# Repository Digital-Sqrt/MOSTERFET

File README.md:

***
# MOSTERFET is covered by the Creative Commons Attribution-ShareAlike 3.0 Unported License.
 Low cost duel MOSFET driver for heated beds and hot ends.  Both Channels are electrically isolated from each other.

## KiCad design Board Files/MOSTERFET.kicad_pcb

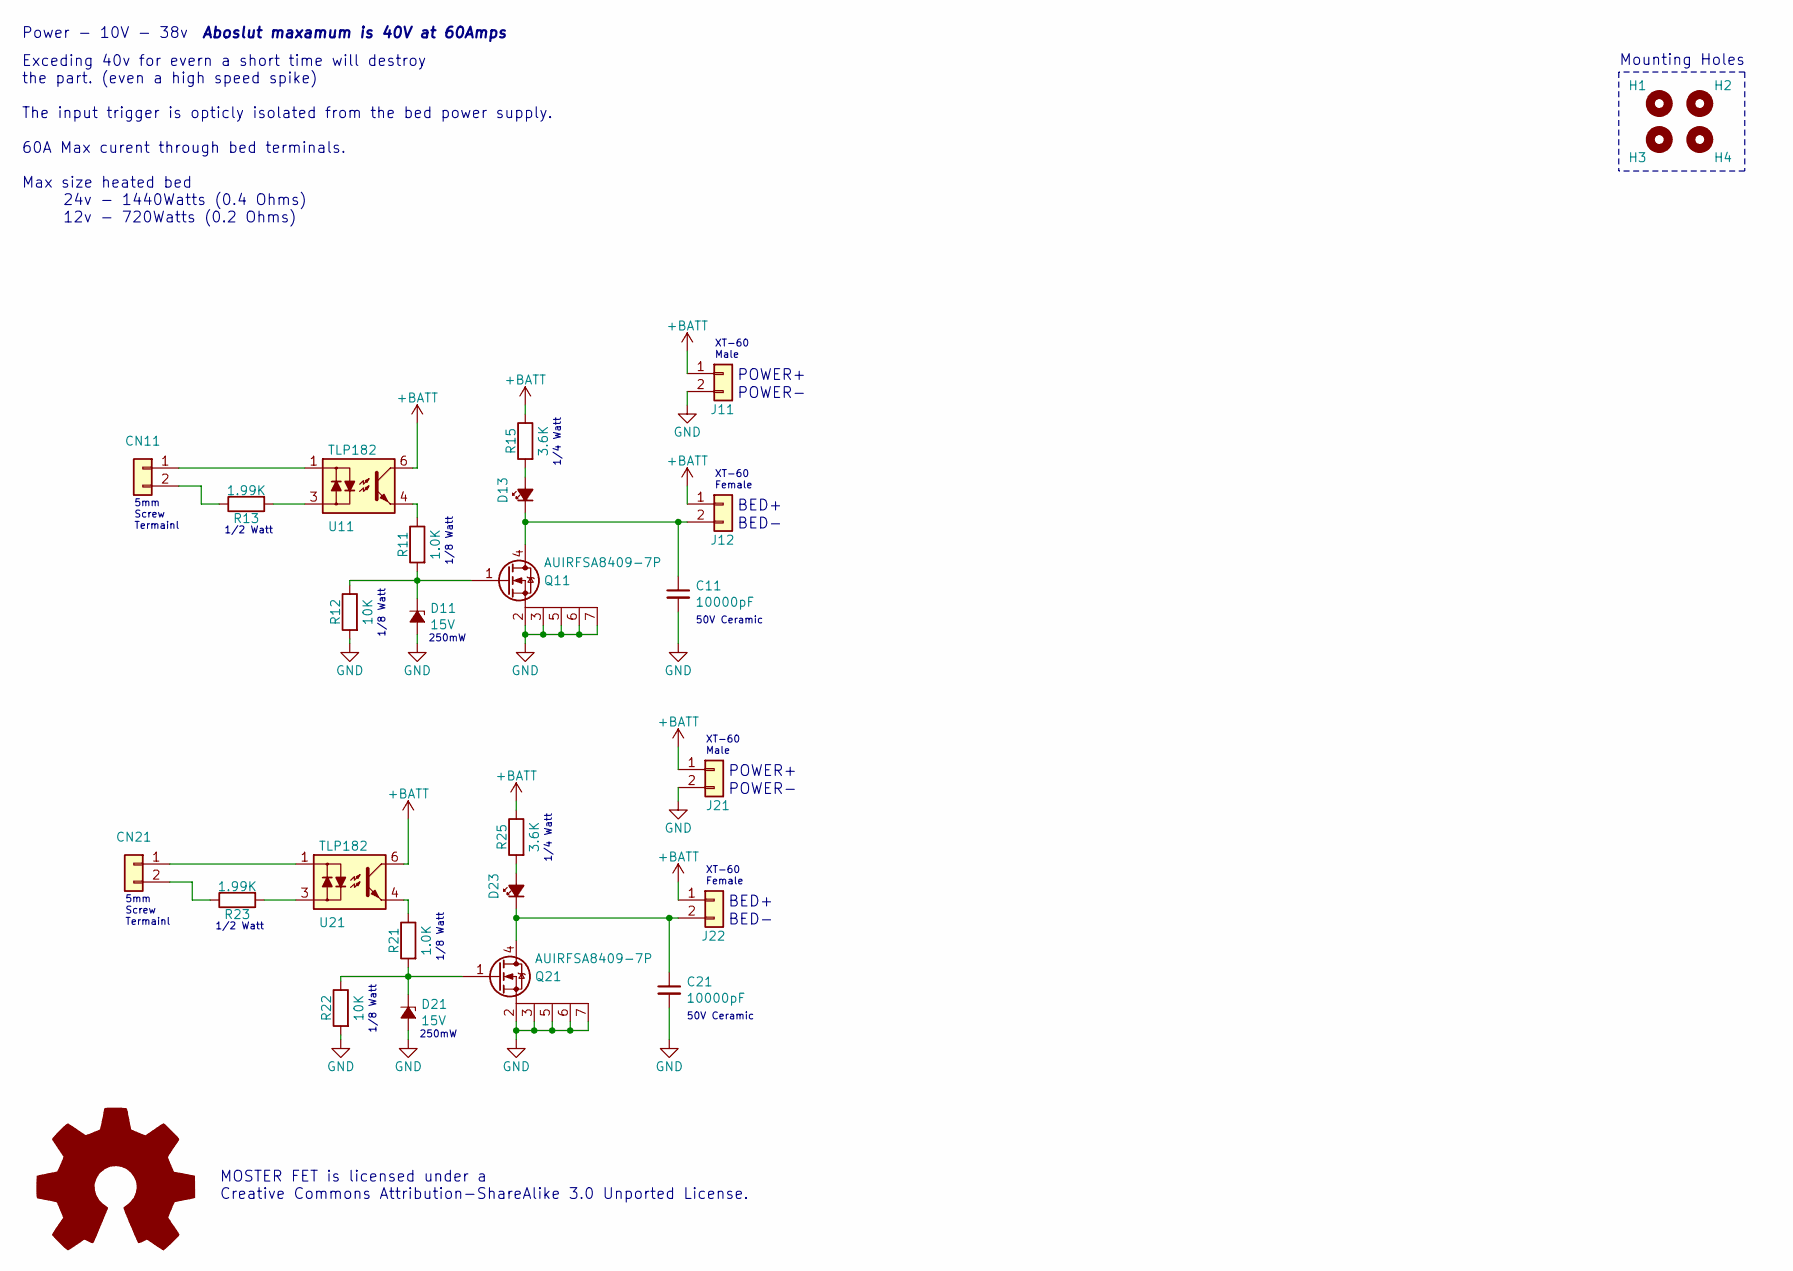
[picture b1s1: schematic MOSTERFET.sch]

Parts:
C11, C21: 10000pF; C_0805_HandSoldering
CN11, CN21: Jumper_NC_Small; JST_NV_B02P-NV_2x5.00mm_Vertical
D11, D21: 15V; SOT-23; Parts Per Reel BZX84C15
D13, D23: QBLP631-IW; LED_0805_HandSoldering
H1, H2, H3, H4: M3 Clearance Hole; MountingHole_3.2mm_M3
J11, J21: XT-60-M; XT60
J12, J22: XT-60-F; XT60
LO1: Logo_Open_Hardware_Large; OSHW-Symbol_8.9x8mm_SilkScreen
Q11, Q21: AUIRFSA8409-7P; TO-263-6-HeatSunk
R11, R21: 1.0K; R_1206_HandSoldering
R12, R22: 10K; R_1206_HandSoldering
R13, R23: 1.99K; R_1210_HandSoldering
R15, R25: 3.6K; R_1206_HandSoldering
U11, U21: TLP182

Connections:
+BATT: J11.1, J12.1, J21.1, J22.1, R15.1, R25.1, U11.6, U21.6
GND: C11.2, C21.2, D11.1 (A), D21.1 (A), J11.2, J21.2, Q11.2 (S), Q11.3 (S), Q11.5 (S), Q11.6 (S), Q11.7 (S), Q21.2 (S), Q21.3 (S), Q21.5 (S), Q21.6 (S), Q21.7 (S), R12.2, R22.2
unnamed: C11.1, D13.1 (K), J12.2, Q11.4 (D)
unnamed: C21.1, D23.1 (K), J22.2, Q21.4 (D)
unnamed: CN11.1, U11.1
unnamed: CN11.2, R13.1
unnamed: CN21.1, U21.1
unnamed: CN21.2, R23.1
unnamed: D11.3 (K), Q11.1 (G), R11.2, R12.1
unnamed: D13.2 (A), R15.2
unnamed: D21.3 (K), Q21.1 (G), R21.2, R22.1
unnamed: D23.2 (A), R25.2
unnamed: R11.1, U11.4
unnamed: R13.2, U11.3
unnamed: R21.1, U21.4
unnamed: R23.2, U21.3

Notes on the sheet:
POWER-
POWER+
BED+
BED-
1/4 Watt
1/8 Watt
1/2 Watt
Exceding 40v for evern a short time will destroy the part. (even a high speed spike) The input trigger is opticly isolated from the bed power supply. 60A Max curent through bed terminals. Max size heated bed 24v - 1440Watts (0.4 Ohms) 12v - 720Watts (0.2 Ohms)
Power - 10V - 38v
Aboslut maxamum is 40V at 60Amps
50V Ceramic
XT-60 Female
XT-60 Male
5mm Screw Termainl
250mW
Mounting Holes
MOSTER FET is licensed under a Creative Commons Attribution-ShareAlike 3.0 Unported License.

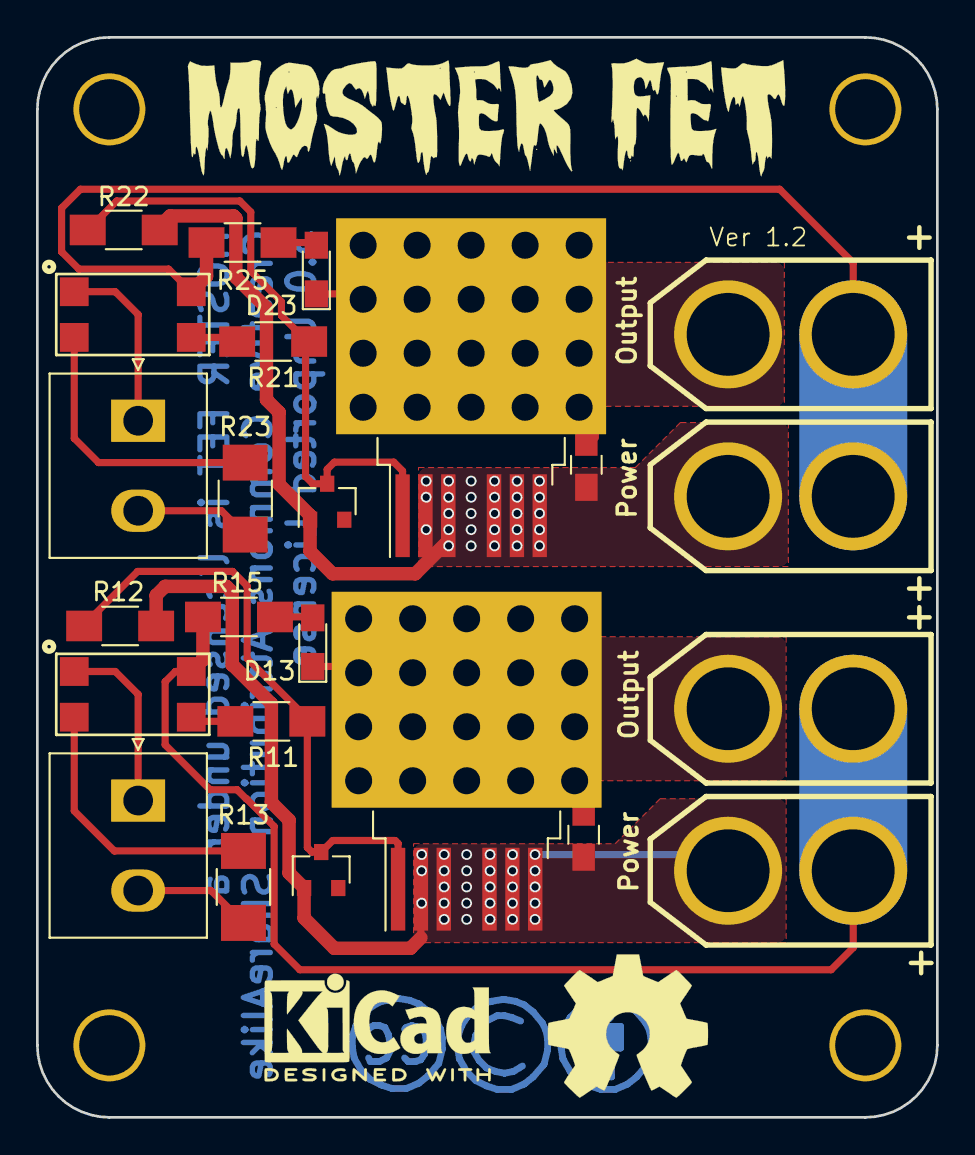
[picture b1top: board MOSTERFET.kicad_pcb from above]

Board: 2 copper layers, 50.0 x 60.0 mm, 29 parts (0 on the bottom side), 16 nets.

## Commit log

2020-03-15 Updated to be about the MOSTER FET
2020-03-15 Trying to Add Web page
2020-03-15 Remove html file
2020-03-15 Set theme jekyll-theme-minimal
2020-03-15 Trying to get a web page
2020-03-15 Removing Files
2020-03-15 Removed OSHW
2020-03-15 New Media Files
2020-03-15 Removed Extra stuff
2020-03-15 Moving Files
2020-03-15 Move Files
    Moving Files to clean Up the Page
2020-03-15 Fixed footprint reference
    Fixed footprint Reference for open harware symbole
2020-03-16 Fixed Errors
    Fixed some rendering errors and some placment errors
2020-03-16 New Pictures
    added more pictures for web page
2020-03-16 Fixed BOM
    Bom was bad
2020-03-16 Changed Board Color
    Updated board color to what was ordered
2020-03-17 added Jpeg versions
2020-03-17 new pic
2020-03-19 Reduced heat sink size
    Reduced heat sink size
    Made logo bigger
    reduce circuit size
2020-03-20 Update Bom and make text file of html
2020-03-21 Removed files
2020-03-21 changed picture
2020-03-24 fixed Board error
2020-03-24 Added Bleed resistot
2020-03-24 Updated picture with bleed resistor
2020-03-25 Added pictures
2020-03-28 Added 2 Parts to LIB
2020-03-28 Found minro error on schmatic
    added wattage to belled off resistor
2020-03-28 Rounded Corners to be more like the example board
    Rounded Corners to be more like the example board
2020-03-29 cleaned up baord files
2020-03-29 Updated Schmatic
2020-04-11 Added OSHWA number to board and documents
2020-05-14 LED not on placment diagrams
    LED Value was ~ needed to be a part number so they showed up in the graphical bom
2020-09-01 Adding Step files for parts
2020-12-05 Adding case files
2020-12-05 Update board_dimensions.png
    updated dim file
2021-02-19 New step file for construction and updates to meda and doc
2021-08-10 Moved components for better diode soldering
